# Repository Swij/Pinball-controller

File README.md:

# Pinball-controller
## Repository structure
* __controller-PCB__ - The kicad PCB design for the controller board.
* __src__ - LUA source code to be run with NodeMcu on the ESP8266.

## Todo
#### PCB-design
* Calculate more precise values for transistor resistors.
* New design for Stern pinball machines.
* Find better solution for I/O shortage on ESP12-E.
* Minified design for factory manufacturing.

#### Firmware
* Make decision on which OS to use on ESP8266. NodeMcu, FreeRTOS, IoTcore etc.
* Communication method/protocol with server.
* Menu traversing method.

#### Master server
* Decide on which language to use. NodeJS, Python, PHP etc.
* Master server locally on for example Raspberry PI or on the internet with a VPS.

#### Payment solution
* Evaluate Swish API.
* Look at other payment solutions such as Strip, Paypal, Braintree etc.
* Decide if we should have an account balance system or only direct payments.

## Ideas
* RFID/NFC reader mounted at the coin machine. Swipe card/tag/phone to pay from balance.

## Kicad dependencies
To view the design in Kicad you need [kicad-ESP8266](https://github.com/jdunmire/kicad-ESP8266) and [Walters kicad libraries](http://smisioto.no-ip.org/elettronica/kicad/kicad-en.htm)

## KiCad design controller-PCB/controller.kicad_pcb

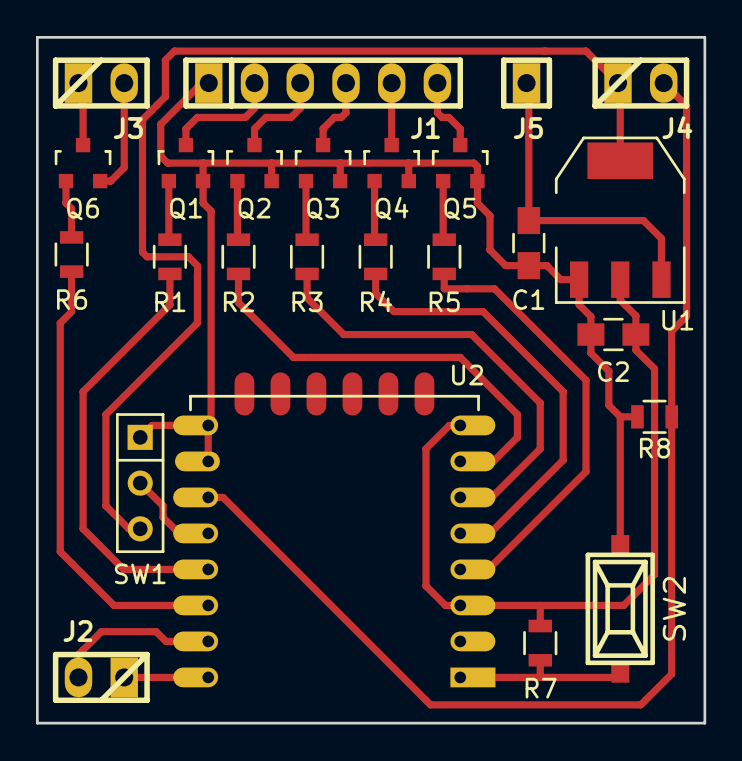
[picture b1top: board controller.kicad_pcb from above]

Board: 2 copper layers, 37.1 x 38.1 mm, 25 parts (0 on the bottom side), 27 nets.

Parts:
C1, C2: 10uF; C_0805_HandSoldering
J1: Pinball I/O; pin_strip_6
J2: UART; pin_strip_2
J3: DOOR-IO; pin_strip_2
J4: DOOR-SW; pin_strip_2
J5: 12V; pin_strip_1
Q1, Q2, Q3, Q4, Q5, Q6: NPN_BEC; SOT-23
R1, R2, R3, R4, R5, R6: 1kΩ; R_0805
R7, R8: 10kΩ; R_0805
SW1: FLASH; SW_Micro_SPST
SW2: smd_push
U1: LM1117-3.3; SOT-223
U2: ESP-12E

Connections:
+12V: C1.1, J5.1, U1.3
/COIN: J1.2, Q1.3
/Pinball-SW1: J1.6, Q5.3
/Pinball-SW2: J1.5, Q4.3
/Pinball-SW3: J1.4, Q3.3
/Pinball-SW4: J1.3, Q2.3
/RXD: J2.2, U2.21
/TXD: J2.1, U2.22
DOOR-SW: J4.2, R8.1, U2.17
FLASH: SW1.2, U2.18
GND: C1.2, C2.2, J1.1, Q1.2, Q2.2, Q3.2, Q4.2, Q5.2, R8.2, SW1.1, SW2.2, U1.1, U2.15, U2.16
unnamed: J3.1, Q6.3
unnamed: J3.2, Q6.2
unnamed: Q1.1, R1.1
unnamed: Q2.1, R2.1
unnamed: Q3.1, R3.1
unnamed: Q4.1, R4.1
unnamed: Q5.1, R5.1
unnamed: Q6.1, R6.1
unnamed: R1.2, U2.19
unnamed: R2.2, U2.7
unnamed: R3.2, U2.6
unnamed: R4.2, U2.5
unnamed: R5.2, U2.4
unnamed: R6.2, U2.20
unnamed: R7.2, SW2.1, U2.1
VCC: C2.1, J4.1, R7.1, SW1.3, U1.2, U1.4, U2.3, U2.8

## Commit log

2016-11-27 Added PCB files and .gitignore
2016-11-29 Added a README file with some relevant information and the first bit of test-code in init.lua
2016-11-29 Made the PCB design tighter and single layer
2016-11-30 Removed net and project files because they are supposed to be ignored.
2016-11-30 Made some minor changes to the PCB design and schematic.
2016-11-30 Corrected the values of the regulator capacitors and added one on the output.
